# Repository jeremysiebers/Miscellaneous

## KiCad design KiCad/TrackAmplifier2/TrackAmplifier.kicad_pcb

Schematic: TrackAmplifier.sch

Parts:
C1, C2, C5, C8, C11, C12, C13, C19, C23, C26, C32, C34, C36, C38, C39: 4.7u; C_1206_3216Metric; Farnell 2320886
C3, C4, C7, C9, C10, C14, C15, C20, C22, C24, C27, C28, C29, C30, C31, C33, C35, C37: 100n; C_1206_3216Metric; Farnell 1414715
C6: 470u; CP_Radial_D10.0mm_P5.00mm; Farnell 2750201
C16: 220u; CP_Radial_D6.3mm_P2.50mm; Farnell 2346568
C17, C18: 10n; C_1206_3216Metric; Farnell 9406549
C21: 220u; CP_Elec_8x10.5
D1: LED GR RUN; LED_0.8x0.8; Farnell 2426215
D2: LED YE WAR; LED_0.8x0.8; Farnell 2426218
D3: LED RD ERR; LED_0.8x0.8; Farnell 2426211
D4: LED GR RX; LED_0.8x0.8; Farnell 2426215
D5, D6, D9, D10, D14, D15: 1n4148; D_1206_3216Metric; Farnell 2677464
D7, D11, D12: VS-6ESH06-M3; TO-277A; Farnell 2471194
D8: LED GR TX; LED_0.8x0.8; Farnell 2426215
D13: LED BL ?; LED_0.8x0.8
D16: LED BL OCC; LED_0.8x0.8; Farnell 2426212
F1: 2.5A; Fuse_2920_7451Metric; Farnell 2834923
FL1, FL2: EMI_Filter_CMode; Choke_EPCOS_B82722-A2302-N1-22.3x22.7mm
J1: DB15_Male_MountingHoles; DSUB-15_Male_Horizontal_P2.77x2.84mm_EdgePinOffset4.94mm_Ho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
J2: Conn_01x06; PinHeader_1x06_P2.54mm_Vertical
MK1: Mounting_Hole; MountingHole_3.7mm_Pad_Via
Q1: NTR5103NT1G; SOT-23; Farnell 2724423
R1, R2, R9, R10, R11, R22: 0E; R_1206_3216Metric; Farnell 1100137
R3, R5, R12, R19, R34, R37: 10E; R_1206_3216Metric; Farnell 1100138
R4, R6, R7, R17, R18, R25, R40, R42: 4k99; R_1206_3216Metric; Farnell 2695161
R8, R14, R30, R39: 1k; R_1206_3216Metric; Farnell 1100192
R13, R15: 39k; R_1206_3216Metric; Farnell 1100234
R16, R38: 3k9; R_1206_3216Metric; Farnell 1100206
R20, R21: 20k; R_1206_3216Metric; Farnell 1100226
R23: 100E; R_1206_3216Metric; Farnell 1100164
R24: 3K3; R_1206_3216Metric; Farnell 1100204
R26, R27, R28, R29, R35, R43, R46: 300E; R_1206_3216Metric; Farnell 1100176
R31: 110k; R_1206_3216Metric; Farnell 1100246
R32, R36: 10K; R_1206_3216Metric; Farnell 1100218
R33, R44, R45: 470; R_1206_3216Metric; Farnell 1100183
R41: 47E; R_1206_3216Metric; Farnell 1100156
R47: NP; R_0603_1608Metric
U1, U2, U5, U6: ST485EBDR; SOIC-8_3.9x4.9mm_P1.27mm
U3: L78M05CDT-1-TO-251-3; TO-251-3-1EP_Horizontal_TabDown; Farnell 1077155
U4: LMD18200; TO-220-11_20.02x17.50mm_P3.4x5.08mm_StaggerOdd_Lead8.45mm_T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
U7: MCP6N11; SOIC-8_3.9x4.9mm_P1.27mm; Farnell 2065857
U8: INA2180; VSSOP-8_3.0x3.0mm_P0.65mm; Farnell 2842970
U9: PIC18F25K40; SOIC-28W_7.5x17.9mm_P1.27mm; Farnell 2564200
U10: MCP1525; SOT-23; Farnell 9758500
U11: MCP9701A-E/TO; TO-92; Farnell 1439484

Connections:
+5V: C10.2, C13.2, C16.1, D5.1, D9.1, J2.2, R1.2, R2.2, R4.2, R9.2, R10.2, R11.2, R12.1, R19.1, R22.1, R32.1, R33.1, R34.1, R40.1, R47.2, U3.3
BMF: C22.2, R18.1, U9.4
BRK: R4.1, U4.4, U9.16
CSEN: R24.2, R25.1, U4.8
CSEN_FLT: C29.2, R25.2, U9.21
DIR: R7.2, U4.3, U9.17
GND: C1.1, C2.1, C3.1, C4.1, C5.1, C6.2, C7.1, C8.1, C9.1, C10.1, C11.1, C12.1, C13.1, C14.1, C15.1, C16.2, C19.1, C20.1, C21.2, C22.1, C23.1, C24.1, C26.1, C27.1, C28.1, C29.1, C30.1, C31.1, C32.1, C33.1, C34.1, C35.1, C36.1, C37.1, C38.1, C39.1, D1.1, D2.1, D3.1, D4.1, D6.2, D8.1, D10.2, D13.1, D16.1, FL2.4, J2.3, Q1.2 (S), R6.1, R7.1, R14.1, R16.2, R24.1, R31.2, R36.2, R38.2, R39.1, U1.2, U1.3, U1.4, U1.5, U2.2, U2.3, U2.4, U2.5, U3.2, U3.4, U4.7, U5.5, U6.2, U6.3, U6.4, U6.5, U7.4, U8.4, U9.8, U9.19, U10.3 (GND), U11.3
GNDD: FL2.3, J1.0, J1.2, J1.8
ICSPCLK: J2.5, U9.27
ICSPDAT: J2.4, U9.28
ID: C30.2, D5.2, D6.1, R30.2, U9.2
ID_R: J1.7, R30.1, R33.2
unnamed: C1.2, C3.2, R1.1, U1.8
unnamed: C2.2, C4.2, R2.1, U2.8
unnamed: C6.1, C8.2, C9.2, F1.1, R17.2, U4.6
unnamed: C11.2, C14.2, R9.1, U5.2, U5.8
unnamed: C12.2, C15.2, R10.1, U6.8
unnamed: C17.1, U4.1
unnamed: C18.2, U4.11
unnamed: C19.2, C20.2, R12.2, R42.1, U7.7
unnamed: C5.2, C7.2, C21.1, D7.3, U3.1
unnamed: C23.2, C24.2, R19.2, U8.8
unnamed: C26.2, C27.2, R22.2, U9.20
unnamed: C31.2, R31.1, R32.2, R44.2
unnamed: C32.2, C33.2, R34.2, U10.1 (IN)
unnamed: C34.2, C35.2, R11.1, U11.1
unnamed: C37.2, Q1.1 (G), R8.2, R36.1, R47.1
unnamed: D1.2, R26.2
unnamed: D2.2, R27.2
unnamed: D3.2, R28.2
unnamed: D4.2, R35.1
unnamed: D7.1, D7.2, R3.2
unnamed: D8.2, R29.2
unnamed: D13.2, R43.1
unnamed: D14.1, D15.1, R23.2
unnamed: D14.2, U8.1
unnamed: D15.2, U8.7
unnamed: D16.2, R46.1
unnamed: FL2.1, J1.10, J1.15
unnamed: R3.1, R5.2
unnamed: R8.1, U1.1
unnamed: R13.1, R15.1, R18.2, U7.6
unnamed: R13.2, U7.1
unnamed: R16.1, R20.1, U7.3
unnamed: R21.2, R38.1, U7.2
unnamed: R26.1, U9.26
unnamed: R27.1, U9.25
unnamed: R28.1, U9.24
unnamed: R29.1, U9.22
unnamed: R35.2, U9.23
unnamed: R37.1, U11.2
unnamed: R42.2, U7.8
unnamed: R43.2, U9.10
unnamed: R46.2, U9.7
OCC: C28.2, R23.1, U9.3
OCC1: C17.2, D11.1, D11.2, D12.3, R41.2, U4.2, U8.3, U8.6
OCC2: D11.3, D12.1, D12.2, FL1.1, R20.2, R41.1, U8.2, U8.5
PWM: R6.2, U4.5, U9.15
PWM2: C18.1, FL1.3, R21.1, U4.10
PWMO1: FL1.2, J1.9
PWMO2: FL1.4, J1.1
RST: Q1.3 (D), R44.1, R45.1, U9.1
RX: U6.1, U9.14
RX_A: J1.12, U6.6
RX_B: J1.4, U6.7
Reset_A: J1.14, U1.6
Reset_B: J1.6, U1.7
SYNC: U2.1, U9.11
Sync_A: J1.13, U2.6
Sync_B: J1.5, U2.7
TEMP: C38.2, R37.2, U9.18
THFLG: R40.2, U4.9, U9.9
TX: U5.4, U9.12
TX_A: J1.11, U5.6
TX_B: J1.3, U5.7
TX_ENA: R14.2, U5.3, U9.13
VPP: J2.1, R45.2
VREF: C39.2, R15.2, U7.5, U9.5, U10.2 (OUT)
Vbus_flt: F1.2, FL2.2, R5.1
Vlm: C36.2, D9.2, D10.1, R17.1, R39.2, U9.6

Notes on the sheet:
Default Drivers Open BRAKE = H PWM = L DIR = X
~MCLR~ Vil = 0.2V Vih = 0.7V LVP is possible, HVP only when "RESET" transceiver input A < B
Disconnected receiver inputs or idle bus will have RO high. Invert for continuous uController reset In order to flash standalone connect the R47 pads
377uA/A --> 4A meauring range 5V / (377^-6 x 4) --> 3K3
length pcb = 104.7mm width pcb = 52mm heart conn to far pcb edge = 35mm Connector heart distance vertical = 75mm horizontal 50mm Connector plate = 39.3mm Space between connector plates = 35.4mm
SMD Vishay resistors: http://nl.farnell.com/w/c/passive-components/resistors-fixed-value/chip-smd-resistors?brand=vishay&resistor-case-style=1206-3216-metric-&packaging=each|cuttape&range=inc-in-stock|exc-delivery-surcharge|exc-obs
3.3V
2.0V
2.1V
2.2V
Output capacitance on REF required between 1 and 10 uF
Farnell: 1467755
OR: 4x MAX3468

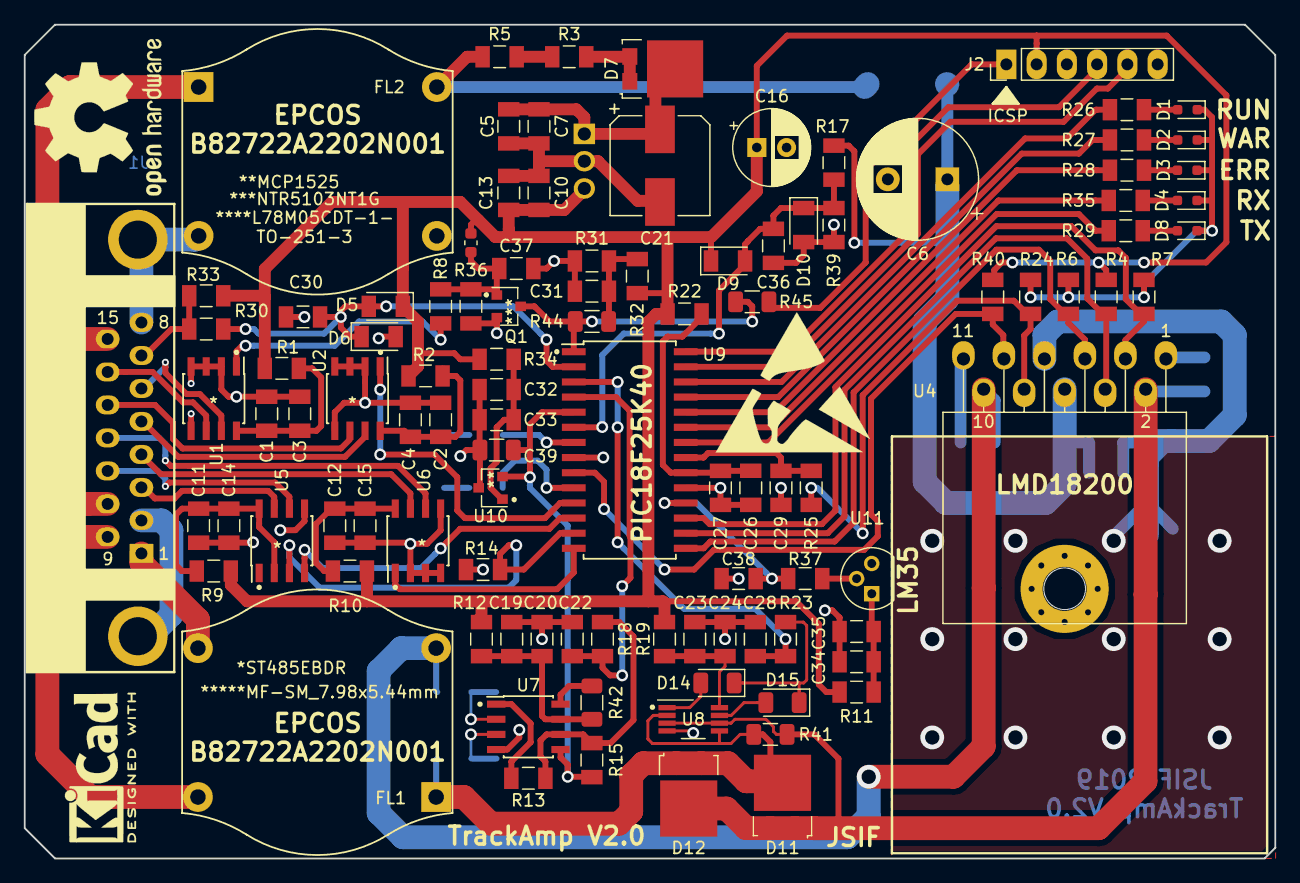
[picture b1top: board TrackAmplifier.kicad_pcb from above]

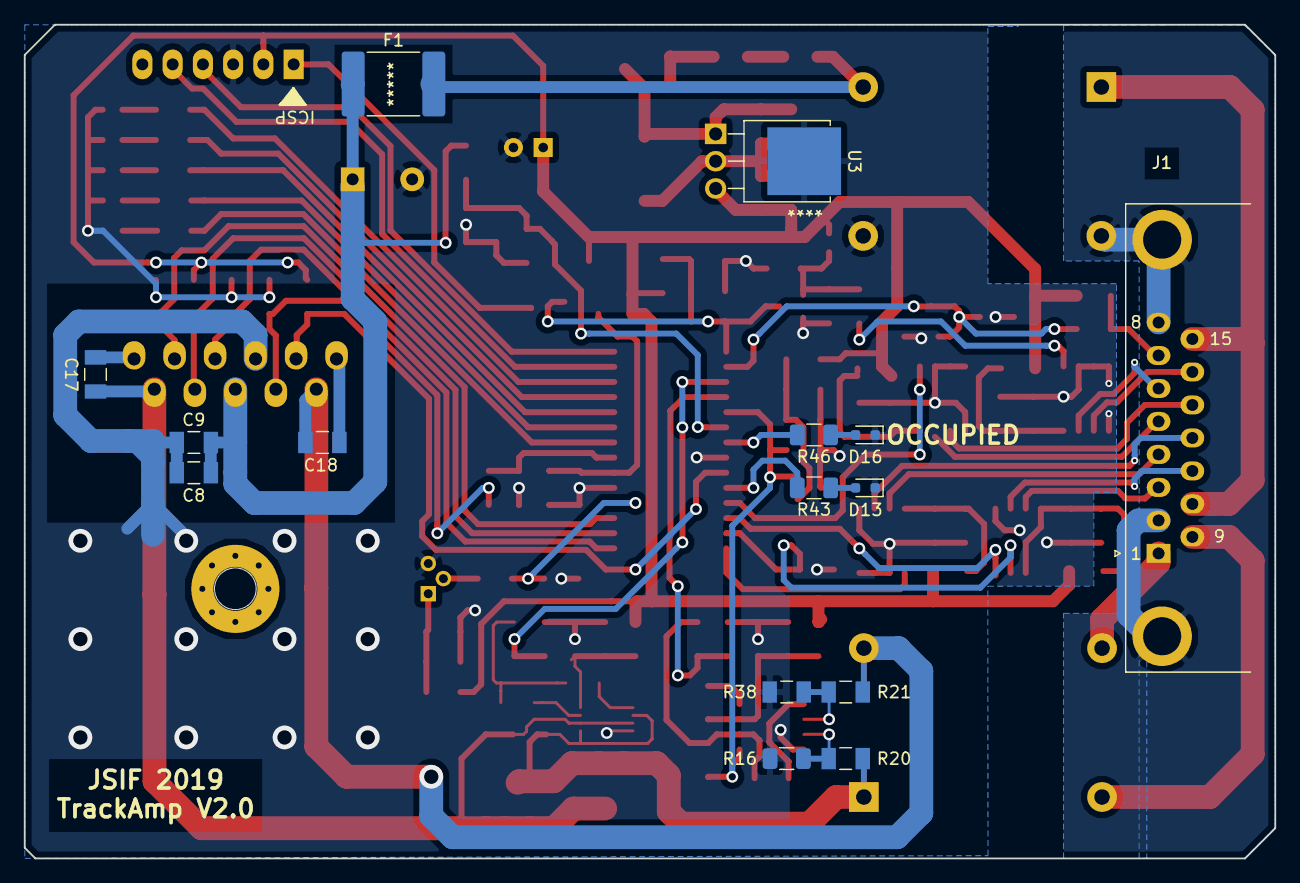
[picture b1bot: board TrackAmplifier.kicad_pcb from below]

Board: 2 copper layers, 105.0 x 70.0 mm, 119 parts (15 on the bottom side), 80 nets.

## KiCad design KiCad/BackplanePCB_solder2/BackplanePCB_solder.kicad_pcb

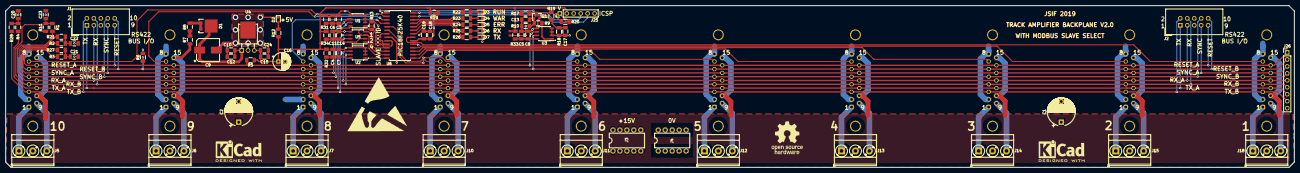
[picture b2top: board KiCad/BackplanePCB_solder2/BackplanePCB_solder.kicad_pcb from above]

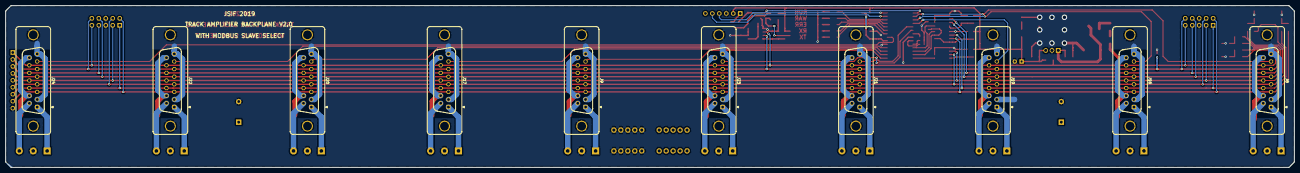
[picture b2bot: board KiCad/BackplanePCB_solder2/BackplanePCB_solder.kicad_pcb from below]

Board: 2 copper layers, 470.0 x 59.0 mm, 98 parts (10 on the bottom side), 78 nets.

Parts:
C1, C2: 470u; CP_Radial_D10.0mm_P7.50mm
C3, C4, C5, C10, C11, C18, C24: 4.7u; C_1206_3216Metric
C6, C7, C8, C12, C13, C14, C15, C17, C19, C20, C21, C22, C23: 100n; C_1206_3216Metric
C9: 220u; CP_Elec_8x10.5
C16: 220u; CP_Radial_D6.3mm_P2.50mm
D1: D_Schottky_AAK; TO-277A
D2, D3: LED GR RUN; LED_0.8x0.8
D4: LED YE WAR; LED_0.8x0.8
D5: LED RD ERR; LED_0.8x0.8
D6: LED GR RX; LED_0.8x0.8
D7: LED GR TX; LED_0.8x0.8
J1, J2: Conn_02x05_Odd_Even; IDC-Header_2x05_P2.54mm_Vertical
J3: PowerBug+15V; DIP-10_W7.62mm
J4: PowerBug_GND; DIP-10_W7.62mm
J5, J6, J7, J10, J11, J12, J13, J14, J15, J18: Conn_01x03; TerminalBlock_Phoenix_MKDS-3-3-5.08_1x03_P5.08mm_Horizontal
J8, J9, J16, J17, J19, J20, J21, J22, J23, J24: DB15_Female_MountingHoles; DSUB-15_Female_Vertical_P2.77x2.84mm_MountingHoles
J25: Conn_01x06; PinHeader_1x06_P2.54mm_Vertical
J26: Conn_01x09; PinHeader_1x09_P2.54mm_Vertical
Q1: NTR5103NT1G; SOT-23
R1, R2, R3, R4, R11, R21, R27, R28: 60E; R_1206_3216Metric
R5, R6: 2k; R_1206_3216Metric
R7, R8: 10E; R_1206_3216Metric
R9, R13: 1k; R_1206_3216Metric
R10, R17: 10k; R_1206_3216Metric
R12, R22, R23, R24, R25, R26: 300E; R_1206_3216Metric
R14, R15, R16: R; R_0603_1608Metric
R18: 110k; R_1206_3216Metric
R19, R20: 470; R_1206_3216Metric
R29, R31, R32, R33, R34: 0E; R_1206_3216Metric
R30: NP; R_0603_1608Metric
U1, U2, U3, U5: ST485EBDR; SOIC-8_3.9x4.9mm_P1.27mm
U4: L78M05CDT-1-TO-251-3; TO-251-3-1EP_Horizontal_TabDown
U6: PIC16F18854-SO; SOIC-28W_7.5x17.9mm_P1.27mm

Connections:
+5V: C15.1, C16.1, C24.1, J25.2, R5.1, R12.1, R17.2, R29.1, R30.1, R31.1, R32.1, R33.1, R34.1, U4.3
+15V: C1.1, C2.1, J3.1, J3.2, J3.3, J3.4, J3.5, J3.6, J3.7, J3.8, J3.9, J3.10, J8.10, J8.15, J9.10, J9.15, J16.10, J16.15, J17.10, J17.15, J19.10, J19.15, J20.10, J20.15, J21.10, J21.15, J22.10, J22.15, J23.10, J23.15, J24.10, J24.15, R7.1
/PWMO1_1: J5.3, J8.9
/PWMO1_2: J6.3, J16.9
/PWMO1_3: J7.3, J19.9
/PWMO1_4: J10.3, J21.9
/PWMO1_5: J11.3, J23.9
/PWMO1_6: J9.9, J12.3
/PWMO1_7: J13.3, J17.9
/PWMO1_8: J14.3, J20.9
/PWMO1_9: J15.3, J22.9
/PWMO1_10: J18.3, J24.9
/PWMO2_1: J5.1, J8.1
/PWMO2_2: J6.1, J16.1
/PWMO2_3: J7.1, J19.1
/PWMO2_4: J10.1, J21.1
/PWMO2_5: J11.1, J23.1
/PWMO2_6: J9.1, J12.1
/PWMO2_7: J13.1, J17.1
/PWMO2_8: J14.1, J20.1
/PWMO2_9: J15.1, J22.1
/PWMO2_10: J18.1, J24.1
GND: C1.2, C2.2, C3.2, C4.2, C5.2, C6.2, C7.2, C8.2, C9.2, C10.2, C11.2, C12.2, C13.2, C14.2, C15.2, C16.2, C17.2, C18.2, C19.2, C20.2, C21.2, C22.2, C23.2, C24.2, D2.1, D3.1, D4.1, D5.1, D6.1, D7.1, J1.5, J1.6, J2.5, J2.6, J4.1, J4.2, J4.3, J4.4, J4.5, J4.6, J4.7, J4.8, J4.9, J4.10, J5.2, J6.2, J7.2, J8.0, J8.2, J8.8, J9.0, J9.2, J9.8, J10.2, J11.2, J12.2, J13.2, J14.2, J15.2, J16.0, J16.2, J16.8, J17.0, J17.2, J17.8, J18.2, J19.0, J19.2, J19.8, J20.0, J20.2, J20.8, J21.0, J21.2, J21.8, J22.0, J22.2, J22.8, J23.0, J23.2, J23.8, J24.0, J24.2, J24.8, J25.3, J26.9, Q1.2, R6.1, R10.2, R13.1, R14.2, R15.2, R16.2, R18.1, U1.2, U1.3, U1.4, U1.5, U2.2, U2.3, U2.4, U2.5, U3.2, U3.3, U3.4, U3.5, U4.2, U4.4, U5.5, U6.8, U6.19
ICSPCLK: J25.5, U6.27
ICSPDAT: J25.4, U6.28
ID_1: J24.7, U6.21
ID_2: J22.7, U6.18
ID_3: J20.7, U6.17
ID_4: J17.7, U6.16
ID_5: J9.7, U6.15
ID_6: J23.7, U6.6
ID_7: J21.7, U6.5
ID_8: J19.7, U6.4
ID_9: J16.7, U6.3
ID_10: J8.7, U6.2
unnamed: C3.1, C6.1, R31.2, U1.8
unnamed: C4.1, C7.1, R32.2, U2.8
unnamed: C5.1, C8.1, R33.2, U3.8
unnamed: C9.1, C10.1, C12.1, D1.3, U4.1
unnamed: C11.1, C14.1, R34.2, U5.2, U5.8
unnamed: C13.1, Q1.1, R9.2, R10.1, R30.2
unnamed: C17.1, R17.1, R18.2, R19.1
unnamed: C18.1, C19.1, R29.2, U6.20
unnamed: C20.1, R4.1, R28.2
unnamed: C21.1, R3.1, R27.2
unnamed: C22.1, R2.1, R21.2
unnamed: C23.1, R1.1, R11.2
unnamed: D1.1, D1.2, R8.2
unnamed: D2.2, R12.2
unnamed: D3.2, R22.2
unnamed: D4.2, R23.2
unnamed: D5.2, R24.2
unnamed: D6.2, R25.2
unnamed: D7.2, R26.2
unnamed: R7.2, R8.1
unnamed: R9.1, U3.1
unnamed: R14.1, U6.7
unnamed: R15.1, U6.10
unnamed: R16.1, U6.9
unnamed: R22.1, U6.26
unnamed: R23.1, U6.25
unnamed: R24.1, U6.24
unnamed: R25.1, U6.23
unnamed: R26.1, U6.22
RESET_A: J1.9, J2.9, J8.14, J9.14, J16.14, J17.14, J19.14, J20.14, J21.14, J22.14, J23.14, J24.14, J26.1, R3.2, R5.2, U3.6
RESET_B: J1.10, J2.10, J8.6, J9.6, J16.6, J17.6, J19.6, J20.6, J21.6, J22.6, J23.6, J24.6, J26.2, R6.2, R27.1, U3.7
RST: Q1.3, R19.2, R20.1, U6.1
RX: U2.1, U6.14
RX_A: J1.3, J2.3, J8.12, J9.12, J16.12, J17.12, J19.12, J20.12, J21.12, J22.12, J23.12, J24.12, J26.5, R1.2, U2.6
RX_B: J1.4, J2.4, J8.4, J9.4, J16.4, J17.4, J19.4, J20.4, J21.4, J22.4, J23.4, J24.4, J26.6, R11.1, U2.7
SYNC: U1.1, U6.11
SYNC_A: J1.7, J2.7, J8.13, J9.13, J16.13, J17.13, J19.13, J20.13, J21.13, J22.13, J23.13, J24.13, J26.3, R2.2, U1.6
SYNC_B: J1.8, J2.8, J8.5, J9.5, J16.5, J17.5, J19.5, J20.5, J21.5, J22.5, J23.5, J24.5, J26.4, R21.1, U1.7
TX: U5.4, U6.12
TX_A: J1.1, J2.1, J8.11, J9.11, J16.11, J17.11, J19.11, J20.11, J21.11, J22.11, J23.11, J24.11, J26.7, R4.2, U5.6
TX_B: J1.2, J2.2, J8.3, J9.3, J16.3, J17.3, J19.3, J20.3, J21.3, J22.3, J23.3, J24.3, J26.8, R28.1, U5.7
TX_ENA: R13.2, U5.3, U6.13
VPP: J25.1, R20.2

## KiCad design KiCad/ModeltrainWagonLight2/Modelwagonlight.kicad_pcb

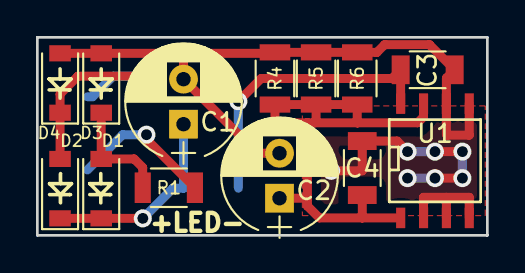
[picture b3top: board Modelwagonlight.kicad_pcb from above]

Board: 2 copper layers, 25.0 x 11.0 mm, 17 parts (0 on the bottom side), 7 nets.

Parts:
C1, C2: 22uF; CP_Radial_D6.3mm_P2.50mm
C3, C4: 100nF; C_1206
D1, D2, D3, D4: STPS0540Z; D_SOD-123
J1, J2, J3, J4: Conn_01x01; Pin_Header_Straight_1x01_Pitch1.00mm
R1: 10R; R_1206
R4, R5, R6: 100R; R_1206
U1: LP2951DR; SOIC-8-N

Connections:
unnamed: C1.1, D1.1, D2.1, J3.1
unnamed: C1.2, C2.2, C3.2, C4.2, D3.2, D4.2, R4.1, R5.1, R6.1, U1.2, U1.3, U1.4, U1.5, U1.6
unnamed: C2.1, C4.1, R4.2, R5.2, R6.2, U1.1, U1.7
unnamed: C3.1, J4.1, U1.8
unnamed: D1.2, D3.1, R1.2
unnamed: D2.2, D4.1, J2.1
unnamed: J1.1, R1.1

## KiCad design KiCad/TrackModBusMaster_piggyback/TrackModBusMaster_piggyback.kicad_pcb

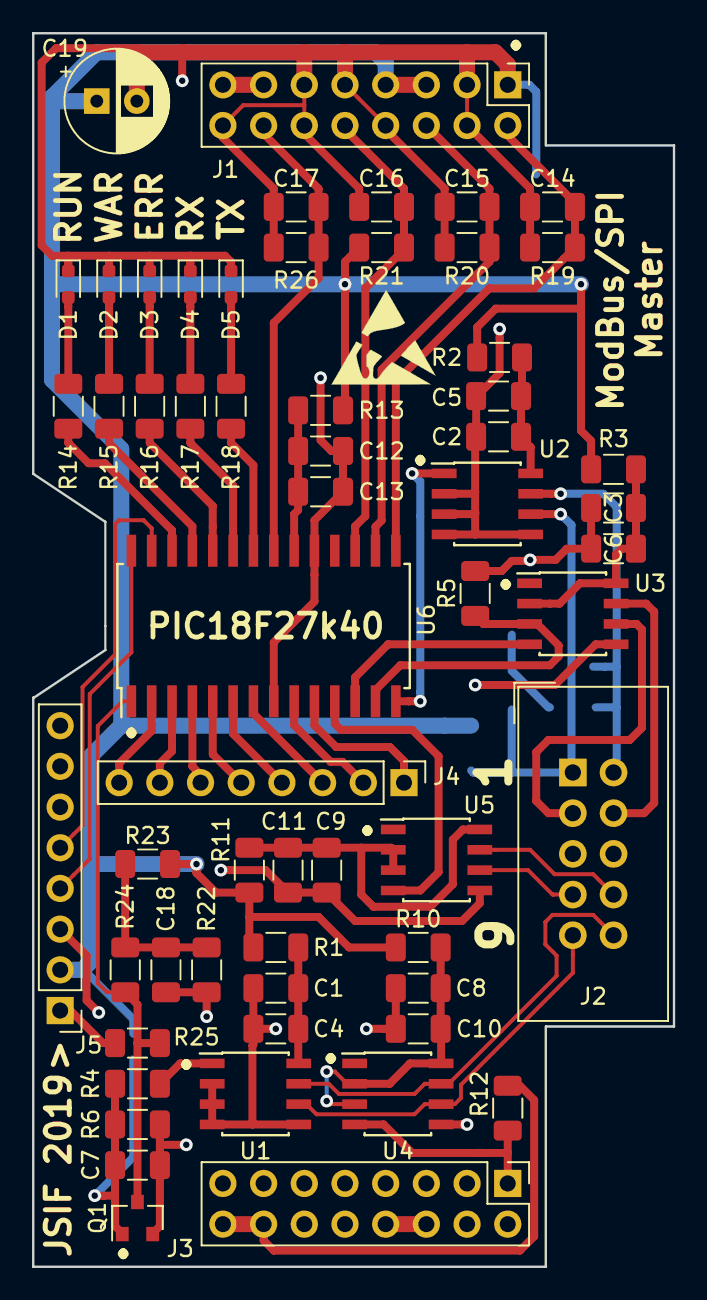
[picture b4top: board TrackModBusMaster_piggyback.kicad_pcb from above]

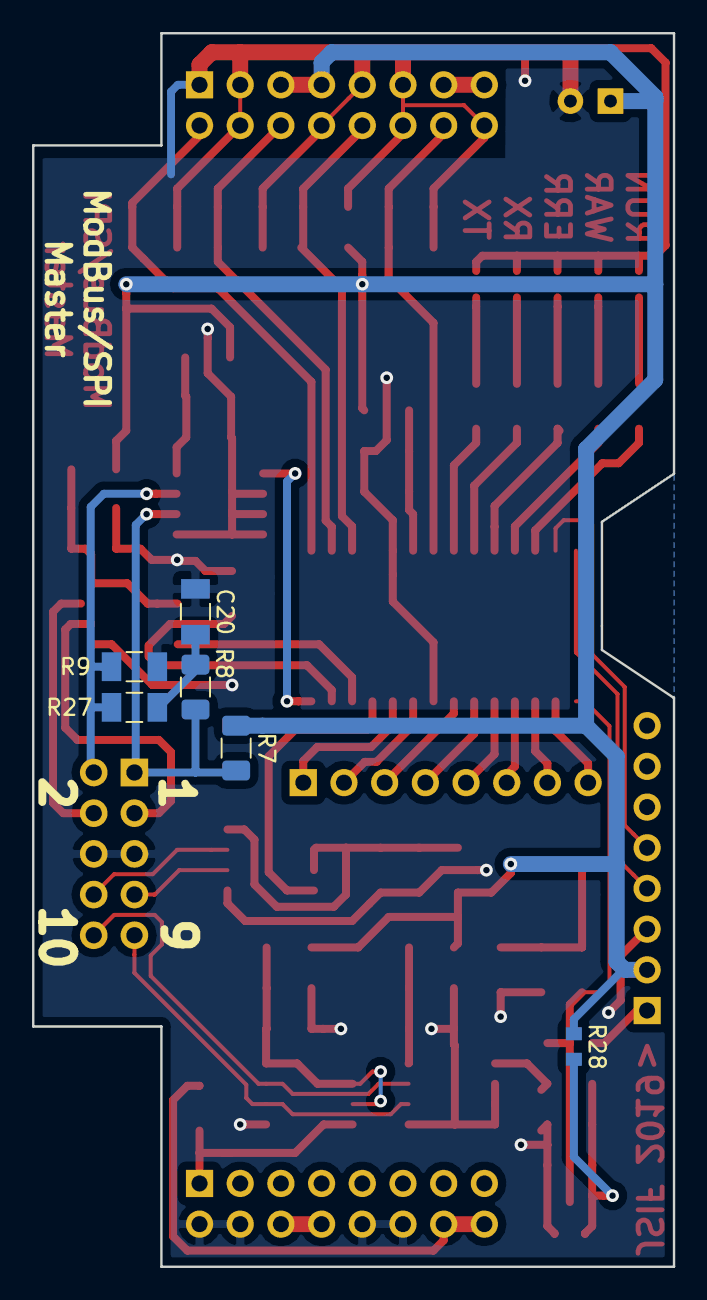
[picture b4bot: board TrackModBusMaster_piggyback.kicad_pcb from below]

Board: 2 copper layers, 40.0 x 77.0 mm, 65 parts (6 on the bottom side), 54 nets.

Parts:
C1, C2, C3, C8, C9, C12, C18: 4.7u; C_1206_3216Metric
C4, C5, C6, C7, C10, C11, C13, C20: 100n; C_1206_3216Metric
C14, C15, C16, C17: 22p; C_1206_3216Metric
C19: 220u; CP_Radial_D6.3mm_P2.50mm
D1, D4, D5: LED GR; LED_0.8x0.8
D2: LED YE; LED_0.8x0.8
D3: LED RD; LED_0.8x0.8
J1, J3: Conn_02x08_Top_Bottom; PinHeader_2x08_P2.54mm_Vertical
J2: Conn_02x05_Odd_Even; IDC-Header_2x05_P2.54mm_Vertical
J4, J5: Conn_01x08; PinHeader_1x08_P2.54mm_Vertical
Q1: NTR5103NT1G; SOT-23
R1, R2, R3, R10, R11, R13: 0E; R_1206_3216Metric
R4, R7, R9: 1k; R_1206_3216Metric
R5, R12, R19, R20, R21, R26: 4k99; R_1206_3216Metric
R6, R23: 10k; R_1206_3216Metric
R8, R27: 60E; R_1206_3216Metric
R14, R15, R16, R17, R18: 300E; R_1206_3216Metric
R22: 110k; R_1206_3216Metric
R24, R25: 470E; R_1206_3216Metric
R28: NP; R_0603_1608Metric
U1, U2, U3, U4, U5: ST485EBDR; SOIC-8_3.9x4.9mm_P1.27mm
U6: PIC18F25K40; SOIC-28W_7.5x17.9mm_P1.27mm

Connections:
+3.3VP: J1.13, J1.15
+3V3: J3.14, J3.16, R12.1
+5V: C19.1, J1.5, J1.7, J5.2, R1.1, R2.1, R3.1, R7.2, R10.1, R11.1, R13.1, R21.1, R23.1, R28.1
+5VP: J3.6, J3.8
GND: C1.2, C2.2, C3.2, C4.2, C5.2, C6.2, C7.2, C8.2, C9.2, C10.2, C11.2, C12.2, C13.2, C14.2, C15.2, C16.2, C17.2, C18.2, C19.2, C20.2, D1.1, D2.1, D3.1, D4.1, D5.1, J1.1, J1.3, J1.4, J1.8, J1.9, J1.11, J1.12, J1.16, J2.5, J2.6, J3.2, J3.4, J3.10, J3.12, J5.3, Q1.2, R5.2, R6.2, R9.1, R19.2, R20.2, R22.2, R26.2, U1.2, U1.3, U1.4, U1.5, U2.2, U2.3, U2.4, U2.5, U3.5, U4.5, U5.5, U6.8, U6.19
ICSPCLK: J5.5, U6.27
ICSPDAT: J5.4, U6.28
unnamed: C1.1, C4.1, R1.2, U1.8
unnamed: C2.1, C5.1, R2.2, U2.8
unnamed: C3.1, C6.1, R3.2, U3.2, U3.8
unnamed: C7.1, Q1.1, R4.1, R6.1, R28.2
unnamed: C8.1, C10.1, R10.2, U4.2, U4.3, U4.8
unnamed: C9.1, C11.1, R11.2, U5.2, U5.3, U5.8
unnamed: C12.1, C13.1, R13.2, U6.20
unnamed: C18.1, R22.1, R23.2, R24.2
unnamed: C20.1, R8.2, R27.2
unnamed: D1.2, R14.1
unnamed: D2.2, R15.1
unnamed: D3.2, R16.1
unnamed: D4.2, R17.1
unnamed: D5.2, R18.1
unnamed: J4.1, U6.10
unnamed: J4.2, U6.9
unnamed: J4.3, U6.7
unnamed: J4.4, U6.6
unnamed: J4.5, U6.5
unnamed: J4.6, U6.4
unnamed: J4.7, U6.3
unnamed: J4.8, U6.2
unnamed: R4.2, U1.1
unnamed: R14.2, U6.26
unnamed: R15.2, U6.25
unnamed: R16.2, U6.24
unnamed: R17.2, U6.23
unnamed: R18.2, U6.22
Reset: Q1.3, R24.1, R25.1, U6.1
Reset_A: J2.9, U1.6, U4.6
Reset_B: J2.10, U1.7, U4.7
Reset_Out: J3.1, R12.2, U4.4
Rx: U2.1, U6.14
Rx_A: J2.1, R7.1, R8.1, U2.6
Rx_B: J2.2, R9.2, R27.1, U2.7
SCK1: C17.1, J1.14, R26.1, U6.21
SDI: C14.1, J1.2, R19.1, U6.15
SDO: C15.1, J1.6, R20.1, U6.16
SS1: C16.1, J1.10, R21.2, U6.17
Sync: U5.4, U6.11
Sync_A: J2.7, U5.6
Sync_B: J2.8, U5.7
Tx: U3.4, U6.12
Tx_A: J2.3, U3.6
Tx_B: J2.4, U3.7
Tx_En: R5.1, U3.3, U6.13
Vpp: J5.1, R25.2

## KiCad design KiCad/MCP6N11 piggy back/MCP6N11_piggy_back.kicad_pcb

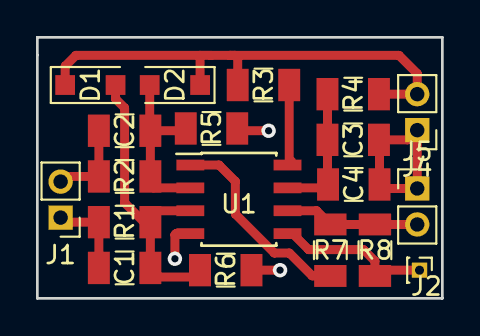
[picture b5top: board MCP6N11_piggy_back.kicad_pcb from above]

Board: 2 copper layers, 22.5 x 14.5 mm, 19 parts (0 on the bottom side), 11 nets.

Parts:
C1, C2: 22p; C_1206_3216Metric
C3: 100n; C_1206_3216Metric
C4: 2.2u; C_1206_3216Metric
D1, D2: 1n4148; D_SOD-123F
J1, J4, J5: Conn_01x02_Male; PinHeader_1x02_P2.00mm_Vertical
J2: Conn_01x01_Male; PinHeader_1x01_P1.00mm_Vertical
R1, R2: 4k99; R_1206_3216Metric
R3: 4k75; R_1206_3216Metric
R4: 10E; R_1206_3216Metric
R5, R6, R7, R8: 1k; R_1206_3216Metric
U1: MCP6N11; SOIC-8_3.9x4.9mm_P1.27mm

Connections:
+5V: D1.1, D2.1, J4.2, R3.2, R4.2
GND: C3.2, C4.2, J4.1, J5.1, R5.1, R6.1, U1.4
unnamed: C1.1, D1.2, R1.1, R6.2, U1.3
unnamed: C1.2, J1.1, R1.2
unnamed: C2.1, D2.2, R2.1, R5.2, U1.2
unnamed: C2.2, J1.2, R2.2
unnamed: C3.1, C4.1, R4.1, U1.7
unnamed: J2.1, R8.1, U1.5
unnamed: J5.2, R7.2, R8.2, U1.6
unnamed: R3.1, U1.8
unnamed: R7.1, U1.1

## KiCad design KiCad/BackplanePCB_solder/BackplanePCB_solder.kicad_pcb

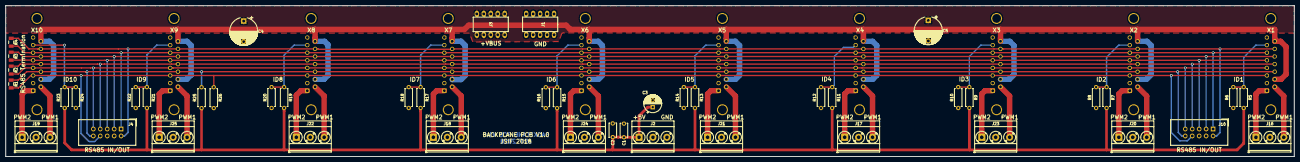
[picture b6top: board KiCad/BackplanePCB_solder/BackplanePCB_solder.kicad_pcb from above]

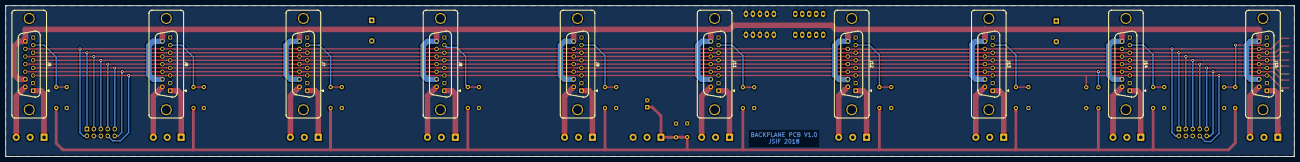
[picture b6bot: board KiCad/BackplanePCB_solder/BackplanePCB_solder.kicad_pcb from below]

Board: 2 copper layers, 470.0 x 55.0 mm, 56 parts (10 on the bottom side), 41 nets.

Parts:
C1: 100n; C_Disc_D5.0mm_W2.5mm_P5.00mm
C2: 22u; C_Disc_D5.0mm_W2.5mm_P5.00mm
C3: 100u; CP_Radial_D6.3mm_P2.50mm
C4, C5: 470u; CP_Radial_D10.0mm_P7.50mm
J1: PowerBug_GND; DIP-10_W7.62mm
J2, J16, J17, J18, J19, J20, J21, J22, J23, J24, J25: Conn_01x03; TerminalBlock_Phoenix_MKDS-3-3-5.08_1x03_P5.08mm_Horizontal
J3: PowerBug+17V; DIP-10_W7.62mm
J4, J10: Conn_02x05_Odd_Even; IDC-Header_2x05_P2.54mm_Vertical
J5, J6, J7, J8, J9, J11, J12, J13, J14, J15: DB15_Female_MountingHoles; DSUB-15_Female_Vertical_P2.77x2.84mm_MountingHoles
R1, R2, R3, R4: 120E; R_1206_3216Metric
R5, R6, R7, R8, R9, R10, R11, R12, R13, R14, R15, R16, R17, R18, R19, R20, R21, R22, R23, R24: R; R_Axial_DIN0207_L6.3mm_D2.5mm_P7.62mm_Horizontal
R25: 4k; R_Axial_DIN0207_L6.3mm_D2.5mm_P7.62mm_Horizontal
R26: 1k; R_Axial_DIN0207_L6.3mm_D2.5mm_P7.62mm_Horizontal

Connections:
+5V: C1.1, C2.1, C3.1, J2.1, R5.2, R7.2, R9.2, R11.2, R13.2, R15.2, R17.2, R19.2, R21.2, R23.2, R25.2
+15V: C4.1, C5.1, J3.1, J3.2, J3.3, J3.4, J3.5, J3.6, J3.7, J3.8, J3.9, J3.10, J5.10, J5.15, J6.10, J6.15, J7.10, J7.15, J8.10, J8.15, J9.10, J9.15, J11.10, J11.15, J12.10, J12.15, J13.10, J13.15, J14.10, J14.15, J15.10, J15.15
/ID_1: J5.7, R5.1, R6.2
/ID_2: J6.7, R7.1, R8.2
/ID_3: J7.7, R9.1, R10.2
/ID_4: J8.7, R11.1, R12.2
/ID_5: J9.7, R13.1, R14.2
/ID_6: J11.7, R15.1, R16.2
/ID_7: J12.7, R17.1, R18.2
/ID_8: J13.7, R19.1, R20.2
/ID_9: J14.7, R21.1, R22.2
/ID_10: J15.7, R23.1, R24.2
/PWMO1_1: J5.9, J16.3
/PWMO1_2: J6.9, J20.3
/PWMO1_3: J7.9, J23.3
/PWMO1_4: J8.9, J17.3
/PWMO1_5: J9.9, J21.3
/PWMO1_6: J11.9, J24.3
/PWMO1_7: J12.9, J18.3
/PWMO1_8: J13.9, J22.3
/PWMO1_9: J14.9, J25.3
/PWMO1_10: J15.9, J19.3
/PWMO2_1: J5.1, J16.1
/PWMO2_2: J6.1, J20.1
/PWMO2_3: J7.1, J23.1
/PWMO2_4: J8.1, J17.1
/PWMO2_5: J9.1, J21.1
/PWMO2_6: J11.1, J24.1
/PWMO2_7: J12.1, J18.1
/PWMO2_8: J13.1, J22.1
/PWMO2_9: J14.1, J25.1
/PWMO2_10: J15.1, J19.1
/RESET_A: J4.2, J5.14, J6.14, J7.14, J8.14, J9.14, J10.2, J11.14, J12.14, J13.14, J14.14, J15.14, R4.2
/RESET_B: J4.1, J5.6, J6.6, J7.6, J8.6, J9.6, J10.1, J11.6, J12.6, J13.6, J14.6, J15.6, R4.1
/RX_A: J4.10, J5.11, J6.11, J7.11, J8.11, J9.11, J10.10, J11.11, J12.11, J13.11, J14.11, J15.11, R1.2, R25.1
/RX_B: J4.8, J5.3, J6.3, J7.3, J8.3, J9.3, J10.8, J11.3, J12.3, J13.3, J14.3, J15.3, R1.1, R26.1
/SYNC_A: J4.3, J5.13, J6.13, J7.13, J8.13, J9.13, J10.3, J11.13, J12.13, J13.13, J14.13, J15.13, R3.2
/SYNC_B: J4.5, J5.5, J6.5, J7.5, J8.5, J9.5, J10.5, J11.5, J12.5, J13.5, J14.5, J15.5, R3.1
/TX_A: J4.7, J5.12, J6.12, J7.12, J8.12, J9.12, J10.7, J11.12, J12.12, J13.12, J14.12, J15.12, R2.2
/TX_B: J4.9, J5.4, J6.4, J7.4, J8.4, J9.4, J10.9, J11.4, J12.4, J13.4, J14.4, J15.4, R2.1
GND: C1.2, C2.2, C3.2, C4.2, C5.2, J1.1, J1.2, J1.3, J1.4, J1.5, J1.6, J1.7, J1.8, J1.9, J1.10, J2.3, J4.4, J4.6, J5.0, J5.2, J5.8, J6.0, J6.2, J6.8, J7.0, J7.2, J7.8, J8.0, J8.2, J8.8, J9.0, J9.2, J9.8, J10.4, J10.6, J11.0, J11.2, J11.8, J12.0, J12.2, J12.8, J13.0, J13.2, J13.8, J14.0, J14.2, J14.8, J15.0, J15.2, J15.8, R6.1, R8.1, R10.1, R12.1, R14.1, R16.1, R18.1, R20.1, R22.1, R24.1, R26.2

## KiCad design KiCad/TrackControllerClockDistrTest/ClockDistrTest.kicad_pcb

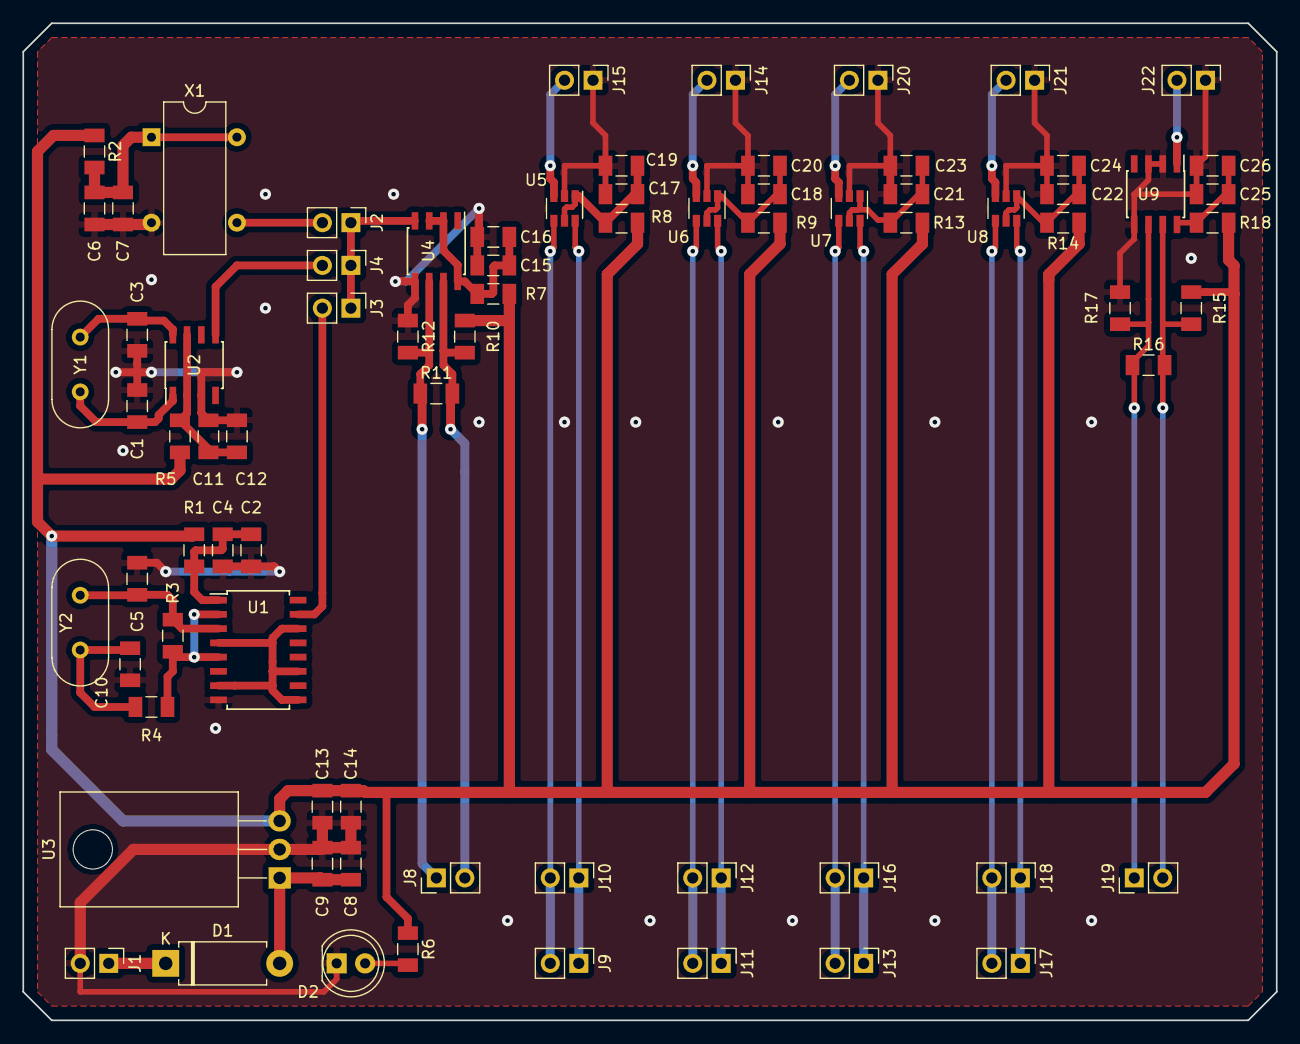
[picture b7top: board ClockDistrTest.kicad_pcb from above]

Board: 2 copper layers, 111.8 x 88.9 mm, 77 parts (0 on the bottom side), 41 nets.

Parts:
C1, C3: 12p; C_1206_3216Metric
C2, C6, C15, C17, C18, C21, C22, C25: 22u; C_1206_3216Metric
C4, C7, C16, C19, C20, C23, C24, C26: 0.1u; C_1206_3216Metric
C5, C10: 10pF; C_1206_3216Metric
C8, C9, C11, C12, C13, C14: C; C_1206_3216Metric
D1: DIODE; D_DO-15_P10.16mm_Horizontal
D2: LED; LED_D5.0mm
J1, J2, J3, J4, J8, J9, J10, J11, J12, J13, J14, J15, J16, J17, J18, J19, J20, J21, J22: Conn_01x02_Male; PinHeader_1x02_P2.54mm_Vertical
R1, R2, R5, R7, R8, R9, R13, R14, R18: 10E; R_1206_3216Metric
R3: 1M; R_1206_3216Metric
R4: 270; R_1206_3216Metric
R6: 300; R_1206_3216Metric
R10, R12, R15, R17: 1K; R_1206_3216Metric
R11, R16: 120E; R_1206_3216Metric
U1: 4049; SOIC-16W_5.3x10.2mm_P1.27mm
U2: NB3N511; SOIC-8_3.9x4.9mm_P1.27mm
U3: LM7805_TO220; TO-220-3_Horizontal_TabDown
U4, U9: MAX14783E; SOIC-8_3.9x4.9mm_P1.27mm
U5, U6, U7, U8: MAX3284E; SOT-23-6
X1: SG-531; Oscillator_SeikoEpson_SG-8002DC
Y1, Y2: Crystal; Crystal_HC49-U_Vertical

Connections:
+5V: C13.1, C14.1, R1.1, R2.1, R5.2, R6.1, R7.2, R8.1, R9.1, R10.2, R13.1, R14.1, R15.2, R18.2, U3.3
/RS422-B: J8.2, R10.1, R11.2, U4.7
A1: J9.1, J10.1, U5.6
A2: J11.1, J12.1, U6.6
A3: J13.1, J16.1, U7.6
A4: J17.1, J18.1, U8.6
B1: J9.2, J10.2, U5.4
B2: J11.2, J12.2, U6.4
B3: J13.2, J16.2, U7.4
B4: J17.2, J18.2, U8.4
GND: C1.2, C2.2, C3.2, C4.2, C5.2, C6.2, C7.2, C8.2, C9.2, C10.2, C11.2, C12.2, C13.2, C14.2, C15.2, C16.2, C17.2, C18.2, C19.2, C20.2, C21.2, C22.2, C23.2, C24.2, C25.2, C26.2, D2.1, J1.2, J14.1, J15.1, J20.1, J21.1, J22.1, R12.1, R17.1, U1.8, U2.3, U3.2, U4.5, U5.2, U6.2, U7.2, U8.2, U9.2, U9.3, U9.5, X1.4
unnamed: C1.1, U2.1, Y1.1
unnamed: C2.1, C4.1, R1.2, U1.1
unnamed: C3.1, U2.8, Y1.2
unnamed: C5.1, R3.2, U1.3, Y2.2
unnamed: C6.1, C7.1, R2.2, X1.1, X1.8
unnamed: C8.1, C9.1, D1.2, U3.1
unnamed: C10.1, R4.1, Y2.1
unnamed: C11.1, C12.1, R5.1, U2.2, U2.7
unnamed: C15.1, C16.1, R7.1, U4.2, U4.3, U4.8
unnamed: C17.1, C19.1, R8.2, U5.1, U5.5
unnamed: C18.1, C20.1, R9.2, U6.1, U6.5
unnamed: C21.1, C23.1, R13.2, U7.1, U7.5
unnamed: C22.1, C24.1, R14.2, U8.1, U8.5
unnamed: C25.1, C26.1, R18.1, U9.8
unnamed: D1.1, J1.1
unnamed: D2.2, R6.2
unnamed: J2.1, J3.1, J4.1, U4.4
unnamed: J2.2, X1.5
unnamed: J3.2, U1.15
unnamed: J4.2, U2.5
unnamed: J8.1, R11.1, R12.2, U4.6
unnamed: J14.2, U6.3
unnamed: J15.2, U5.3
unnamed: J19.1, R16.1, R17.2, U9.6
unnamed: J19.2, R15.1, R16.2, U9.7
unnamed: J20.2, U7.3
unnamed: J21.2, U8.3
unnamed: J22.2, U9.1
unnamed: R3.1, R4.2, U1.2, U1.5
unnamed: U1.4, U1.7, U1.9, U1.11, U1.14

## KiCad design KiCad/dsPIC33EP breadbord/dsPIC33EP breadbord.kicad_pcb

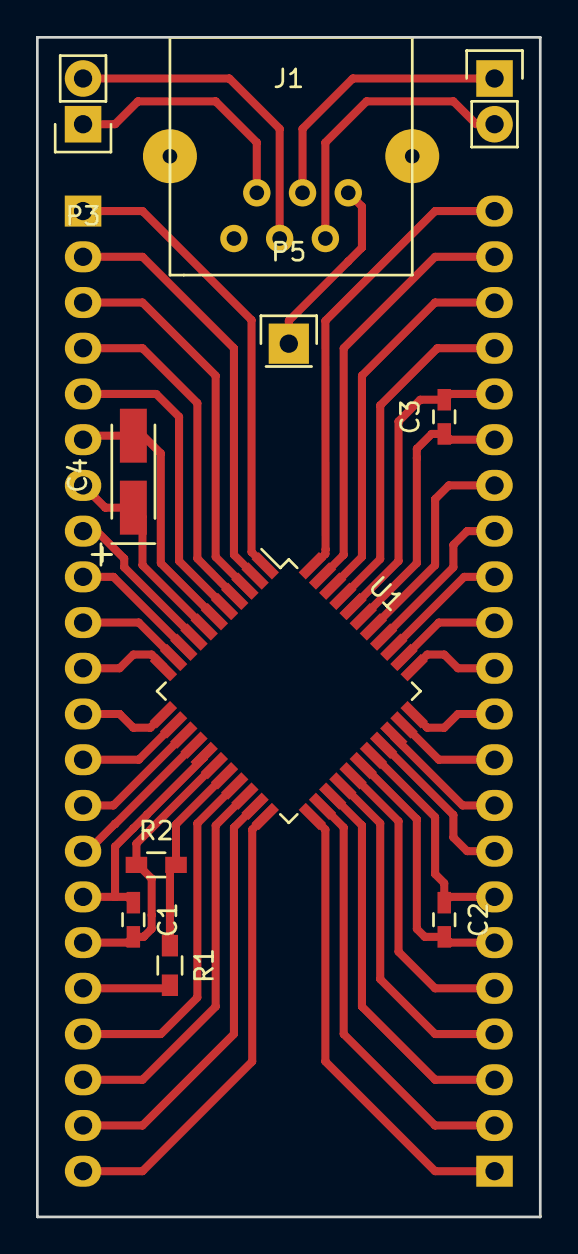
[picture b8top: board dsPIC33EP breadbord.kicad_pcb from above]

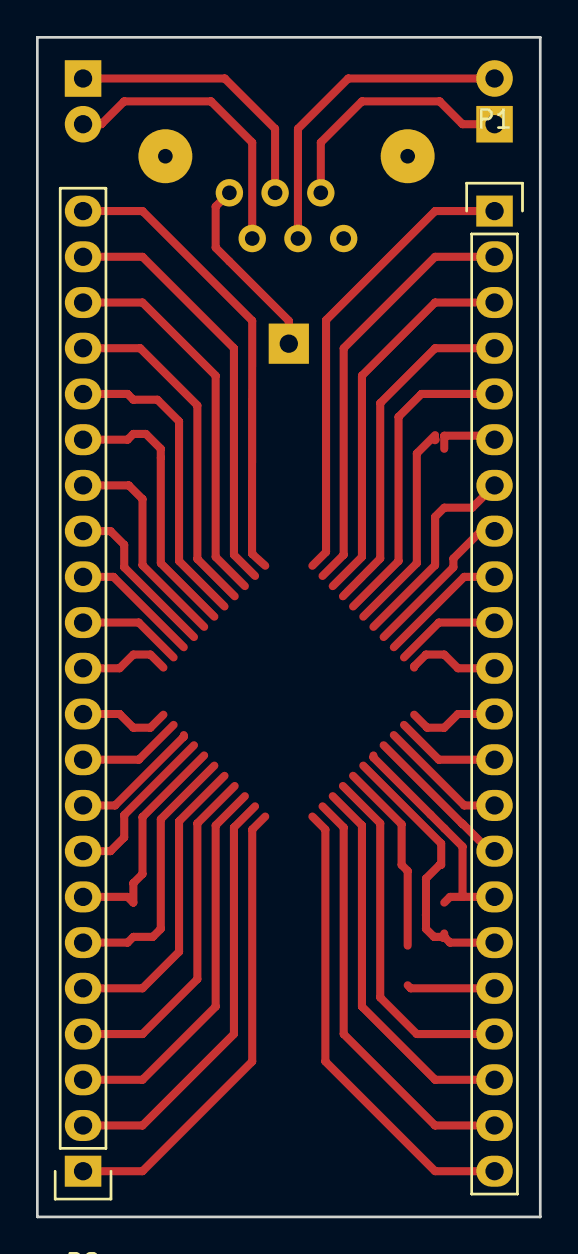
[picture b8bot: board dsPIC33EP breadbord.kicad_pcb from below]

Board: 2 copper layers, 27.9 x 65.5 mm, 13 parts (2 on the bottom side), 50 nets.

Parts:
C1, C2, C3: 100nF; C_0603_HandSoldering
C4: 10uF; TantalC_SizeA_EIA-3216_HandSoldering
J1: RJ12; RJ12_E
P1, P2: CONN_01X22; Pin_Header_Straight_1x22
P3, P4: CONN_01X02; Pin_Header_Straight_1x02
P5: CONN_01X01; Pin_Header_Straight_1x01
R1: 470E; R_0603_HandSoldering
R2: 10K; R_0603_HandSoldering
U1: DSPIC33EP128GM304; LQFP-44_10x10mm_Pitch0.8mm

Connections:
/1: P1.1, U1.1
/2: P1.2, U1.2
/3: P1.3, U1.3
/4: P1.4, U1.4
/5: P1.5, U1.5
/6: C4.2, P1.6, U1.6
/7: C4.1, P1.7, U1.7
/8: P1.8, U1.8
/9: P1.9, U1.9
/10: P1.10, U1.10
/11: P1.11, U1.11
/12: P1.12, U1.12
/13: P1.13, U1.13
/14: P1.14, U1.14
/15: P1.15, U1.15
/16: C1.1, P1.16, U1.16
/17: C1.2, P1.17, R2.1, U1.17
/18: P1.18, R1.2
/19: P1.19, U1.19
/20: P1.20, U1.20
/21: P1.21, U1.21
/22: P1.22, U1.22
/23: P2.1, U1.23
/24: P2.2, U1.24
/25: P2.3, U1.25
/26: P2.4, U1.26
/27: P2.5, U1.27
/28: C2.2, P2.6, U1.28
/29: C2.1, P2.7, U1.29
/30: P2.8, U1.30
/31: P2.9, U1.31
/32: P2.10, U1.32
/33: P2.11, U1.33
/34: P2.12, U1.34
/35: P2.13, U1.35
/36: P2.14, U1.36
/37: P2.15, U1.37
/38: P2.16, U1.38
/39: C3.1, P2.17, U1.39
/40: C3.2, P2.18, U1.40
/41: P2.19, U1.41
/42: P2.20, U1.42
/43: P2.21, U1.43
/44: P2.22, U1.44
/~MCLR~: R1.1, R2.2, U1.18
unnamed: J1.1, P5.1
unnamed: J1.2, P4.2
unnamed: J1.3, P4.1
unnamed: J1.4, P3.2
unnamed: J1.5, P3.1
